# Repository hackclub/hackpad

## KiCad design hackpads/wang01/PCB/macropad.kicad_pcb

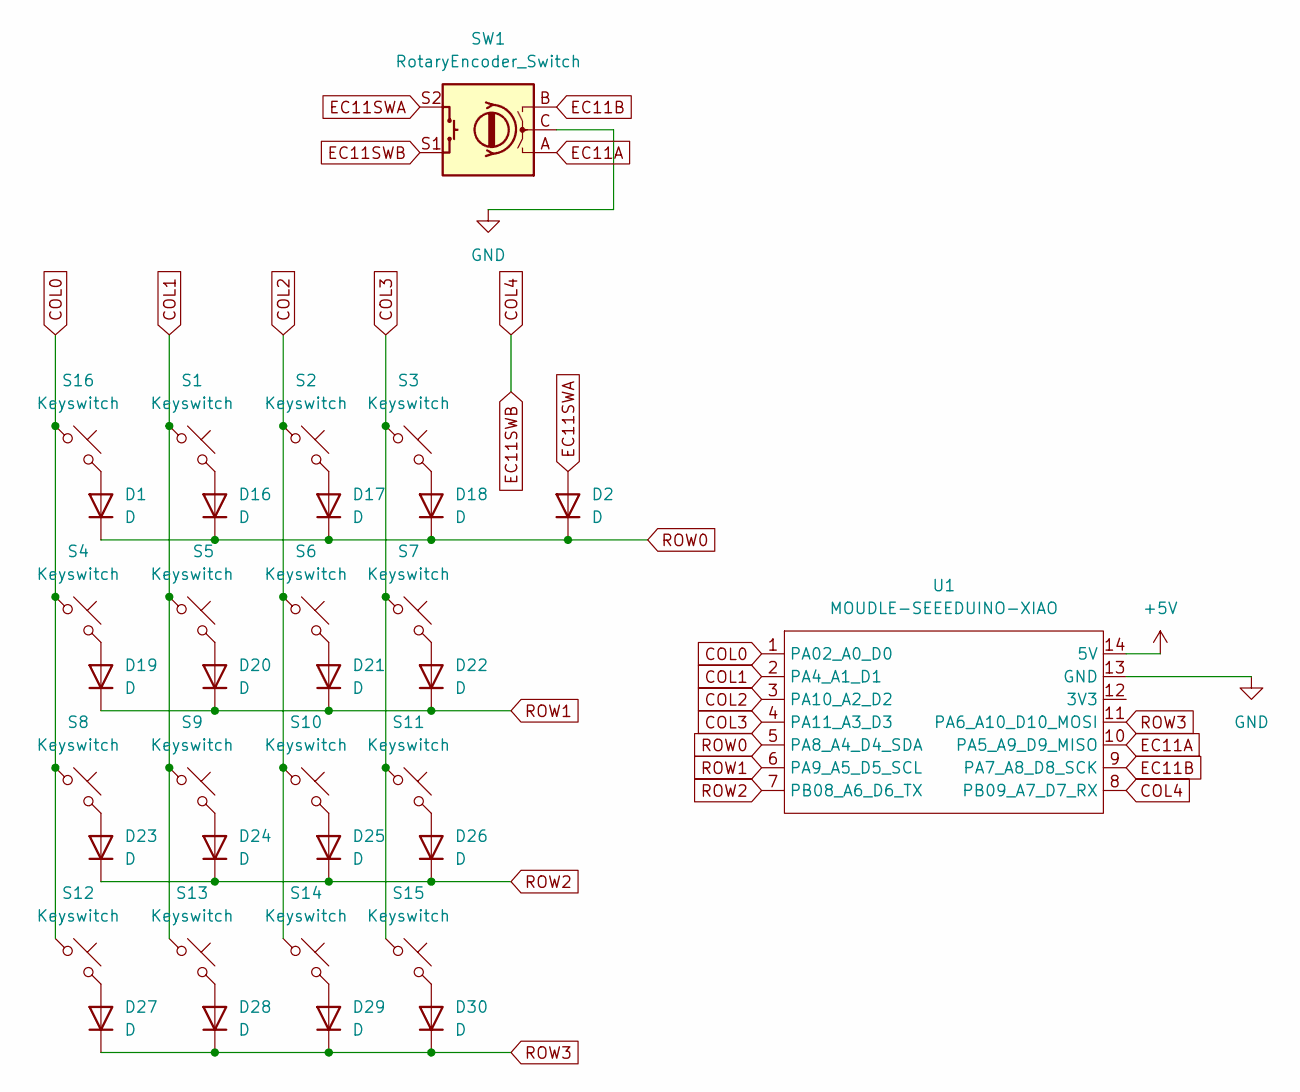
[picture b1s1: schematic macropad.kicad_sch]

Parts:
D1, D2, D16, D17, D18, D19, D20, D21, D22, D23, D24, D25, D26, D27, D28, D29, D30: D; Diode_DO-35
S1, S2, S3, S4, S5, S6, S7, S8, S9, S10, S11, S12, S13, S14, S15, S16: Keyswitch; MX-Solderable-1U
SW1: RotaryEncoder_Switch; RotaryEncoder_Alps_EC11E-Switch_Vertical_H20mm
U1: MOUDLE-SEEEDUINO-XIAO; MOUDLE14P-2.54-21X17.8MM

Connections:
+5V: U1.14 (5V)
COL0: S4.1, S8.1, S12.1, S16.1, U1.1 (PA02_A0_D0)
COL1: S1.1, S5.1, S9.1, S13.1, U1.2 (PA4_A1_D1)
COL2: S2.1, S6.1, S10.1, S14.1, U1.3 (PA10_A2_D2)
COL3: S3.1, S7.1, S11.1, S15.1, U1.4 (PA11_A3_D3)
COL4: SW1.S1, U1.8 (PB09_A7_D7_RX)
EC11A: SW1.A, U1.10 (PA5_A9_D9_MISO)
EC11B: SW1.B, U1.9 (PA7_A8_D8_SCK)
EC11SWA: D2.2 (A), SW1.S2
GND: SW1.C, U1.13 (GND)
unnamed: D1.2 (A), S16.2
unnamed: D16.2 (A), S1.2
unnamed: D17.2 (A), S2.2
unnamed: D18.2 (A), S3.2
unnamed: D19.2 (A), S4.2
unnamed: D20.2 (A), S5.2
unnamed: D21.2 (A), S6.2
unnamed: D22.2 (A), S7.2
unnamed: D23.2 (A), S8.2
unnamed: D24.2 (A), S9.2
unnamed: D25.2 (A), S10.2
unnamed: D26.2 (A), S11.2
unnamed: D27.2 (A), S12.2
unnamed: D28.2 (A), S13.2
unnamed: D29.2 (A), S14.2
unnamed: D30.2 (A), S15.2
ROW0: D1.1 (K), D2.1 (K), D16.1 (K), D17.1 (K), D18.1 (K), U1.5 (PA8_A4_D4_SDA)
ROW1: D19.1 (K), D20.1 (K), D21.1 (K), D22.1 (K), U1.6 (PA9_A5_D5_SCL)
ROW2: D23.1 (K), D24.1 (K), D25.1 (K), D26.1 (K), U1.7 (PB08_A6_D6_TX)
ROW3: D27.1 (K), D28.1 (K), D29.1 (K), D30.1 (K), U1.11 (PA6_A10_D10_MOSI)

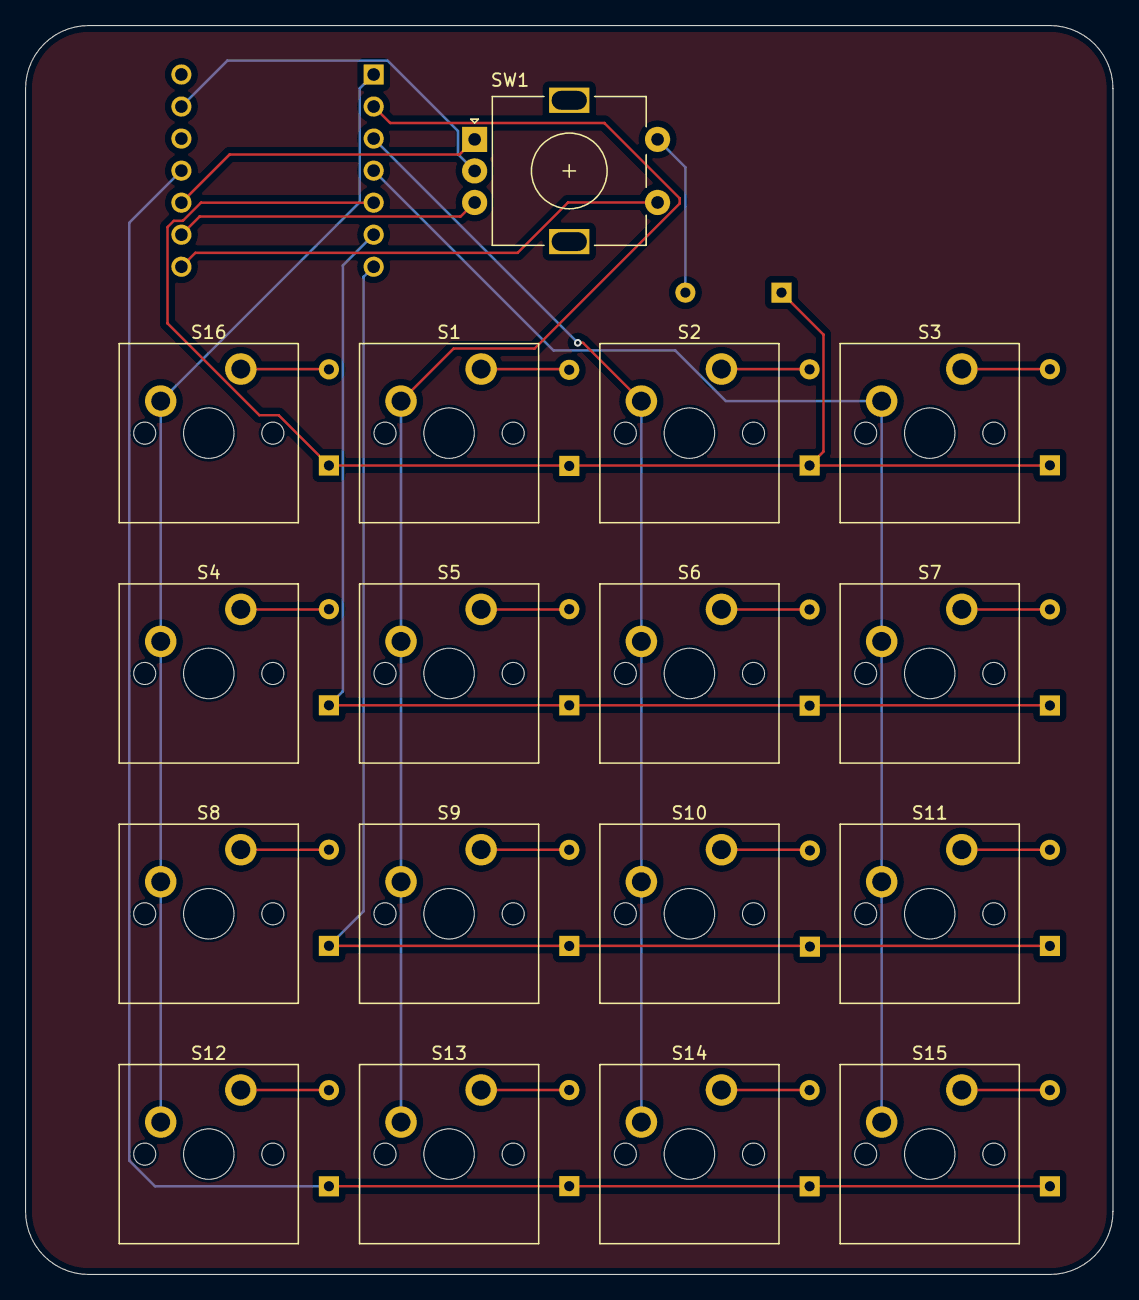
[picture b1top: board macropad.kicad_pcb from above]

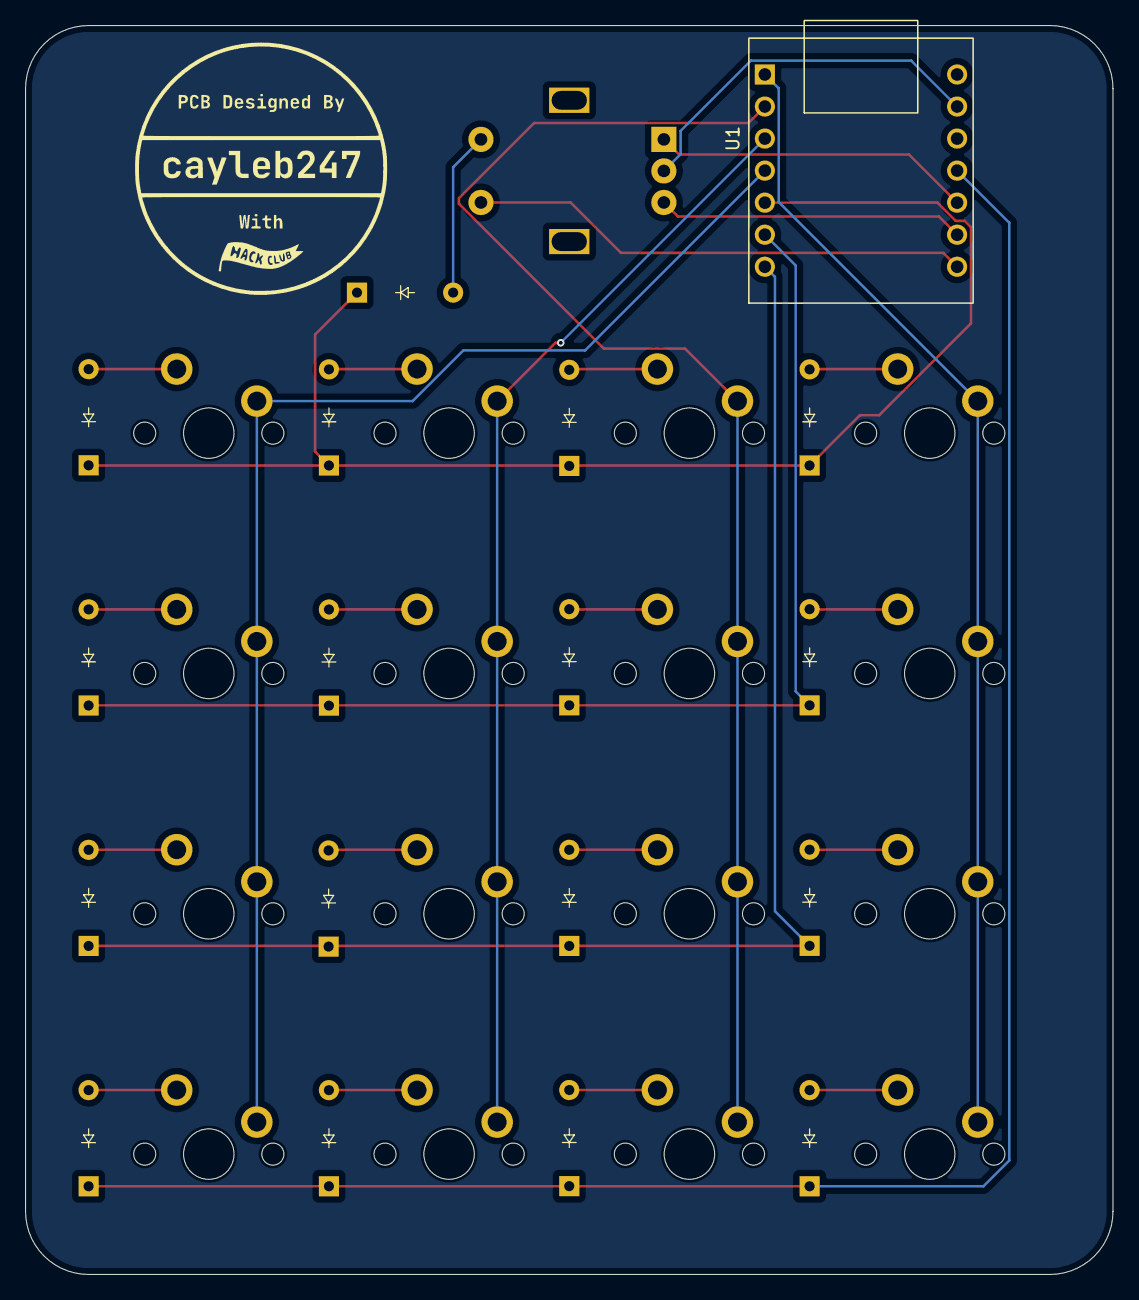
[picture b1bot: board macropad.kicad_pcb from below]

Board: 2 copper layers, 86.2 x 99.0 mm, 35 parts (18 on the bottom side), 29 nets.

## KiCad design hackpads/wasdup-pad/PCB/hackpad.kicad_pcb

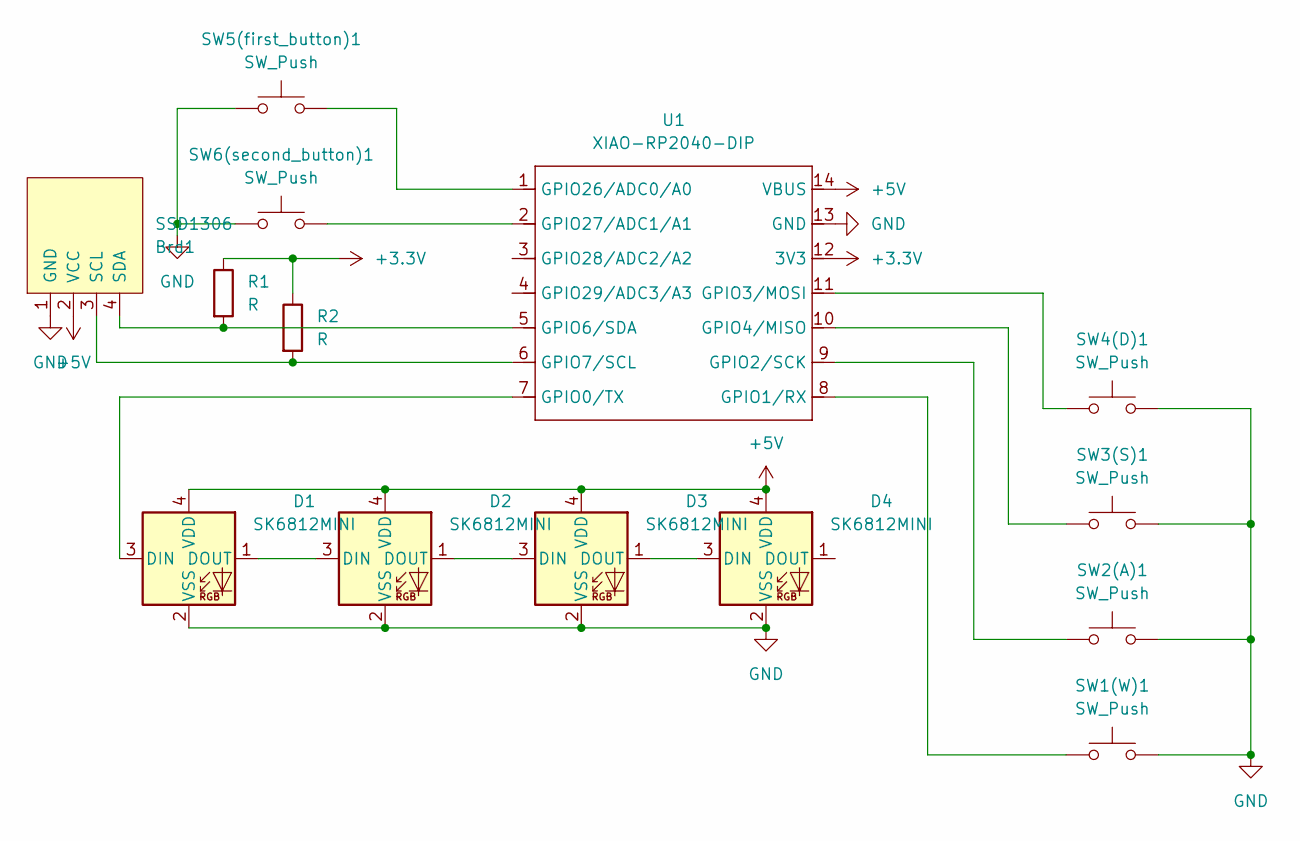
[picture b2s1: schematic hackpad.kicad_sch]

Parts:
Brd1: SSD1306; 128x64OLED
D1, D2, D3, D4: SK6812MINI; LED_SK6812MINI_PLCC4_3.5x3.5mm_P1.75mm
R1, R2: R; R_Axial_DIN0204_L3.6mm_D1.6mm_P7.62mm_Horizontal
SW1(W)1, SW2(A)1, SW3(S)1, SW4(D)1: SW_Push; SW_Cherry_MX_1.00u_PCB
SW5(first_button)1, SW6(second_button)1: SW_Push; SW_PUSH_6mm_H4.3mm
U1: XIAO-RP2040-DIP

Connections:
+3.3V: R1.1, R2.1, U1.12 (3V3)
+5V: Brd1.2 (VCC), D1.4 (VDD), D2.4 (VDD), D3.4 (VDD), D4.4 (VDD), U1.14 (VBUS)
GND: Brd1.1 (GND), D1.2 (VSS), D2.2 (VSS), D3.2 (VSS), D4.2 (VSS), SW1(W)1.2, SW2(A)1.2, SW3(S)1.2, SW4(D)1.2, SW5(first_button)1.1, SW6(second_button)1.1, U1.13 (GND)
unnamed: Brd1.3 (SCL), R2.2, U1.6 (GPIO7/SCL)
unnamed: Brd1.4 (SDA), R1.2, U1.5 (GPIO6/SDA)
unnamed: D1.3 (DIN), U1.7 (GPIO0/TX)
unnamed: D1.1 (DOUT), D2.3 (DIN)
unnamed: D2.1 (DOUT), D3.3 (DIN)
unnamed: D3.1 (DOUT), D4.3 (DIN)
unnamed: SW1(W)1.1, U1.8 (GPIO1/RX)
unnamed: SW2(A)1.1, U1.9 (GPIO2/SCK)
unnamed: SW4(D)1.1, U1.11 (GPIO3/MOSI)
unnamed: SW3(S)1.1, U1.10 (GPIO4/MISO)
unnamed: SW5(first_button)1.2, U1.1 (GPIO26/ADC0/A0)
unnamed: SW6(second_button)1.2, U1.2 (GPIO27/ADC1/A1)

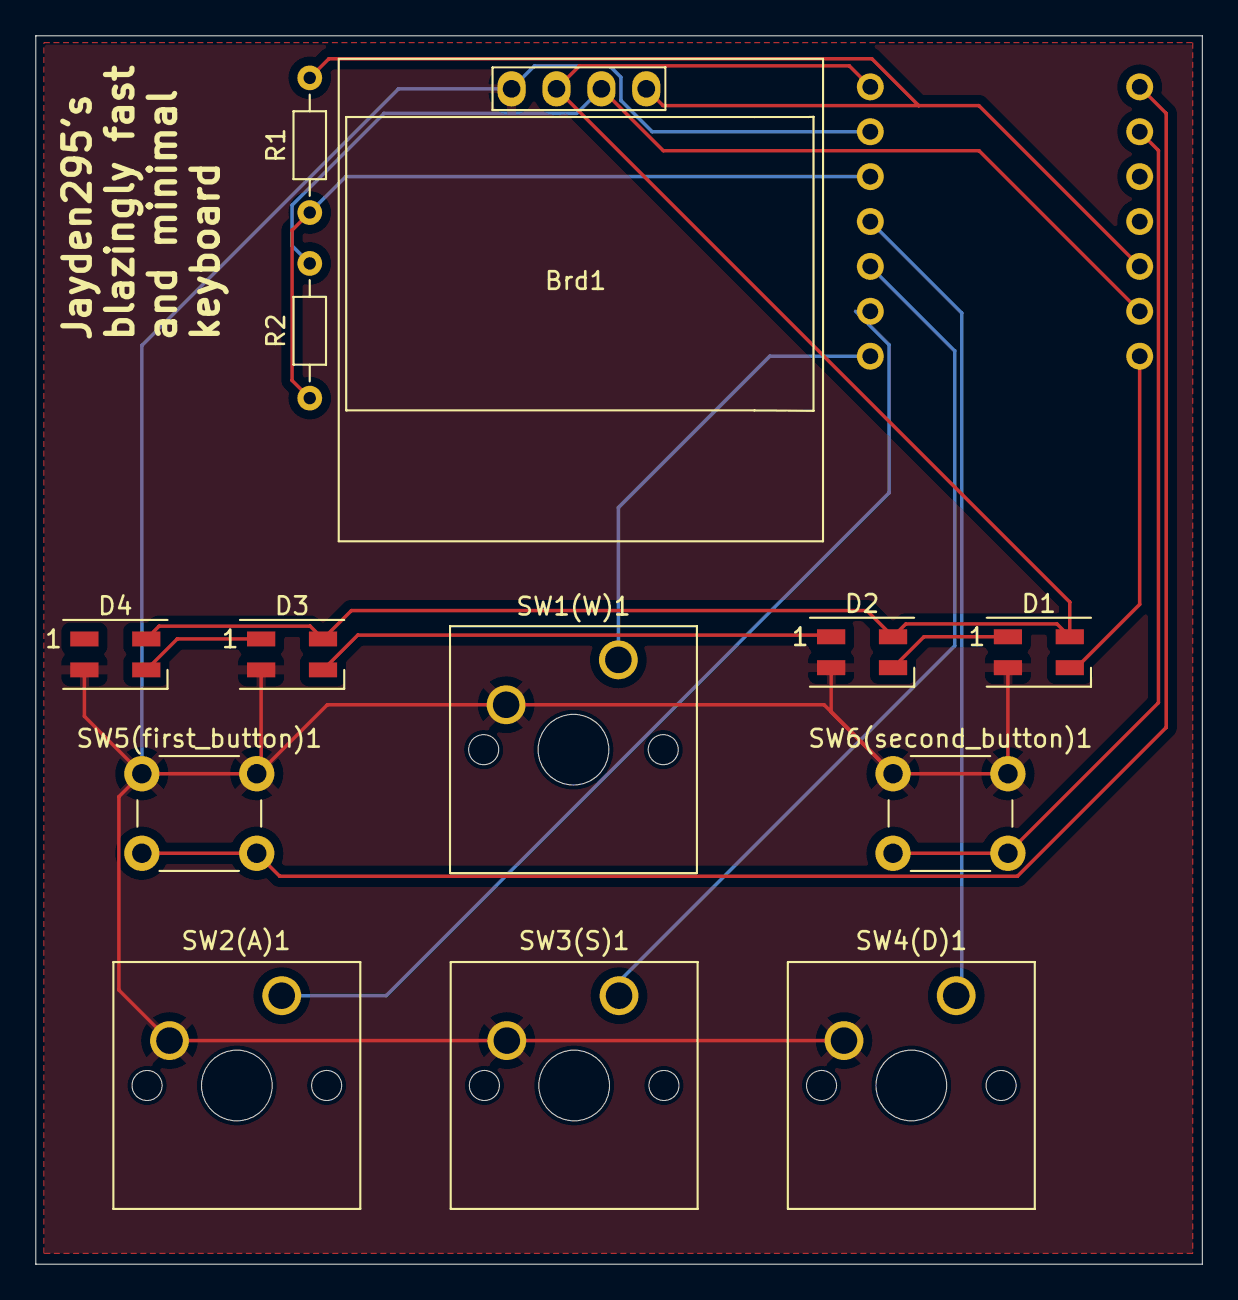
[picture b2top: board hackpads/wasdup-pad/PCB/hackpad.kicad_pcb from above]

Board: 2 copper layers, 66.0 x 69.5 mm, 14 parts (1 on the bottom side), 15 nets.

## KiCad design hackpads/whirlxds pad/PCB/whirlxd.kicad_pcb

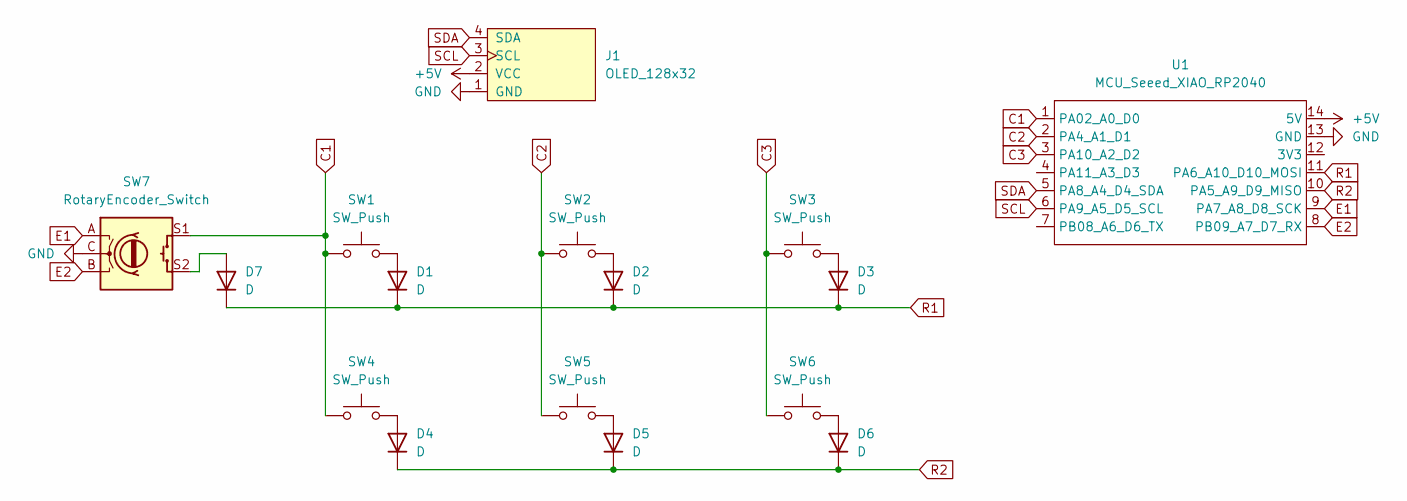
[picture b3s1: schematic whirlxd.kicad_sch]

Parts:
D1, D2, D3, D4, D5, D6, D7: D; D_SOD-523
J1: OLED_128x32; SSD1306-0.91-OLED-4pin-128x32 (2)
SW1, SW2, SW3, SW4, SW5, SW6: SW_Push; SW_Cherry_MX_1.00u_PCB
SW7: RotaryEncoder_Switch; RotaryEncoder_Alps_EC11E-Switch_Vertical_H20mm
U1: MCU_Seeed_XIAO_RP2040; XIAO-RP2040-DIP

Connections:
+5V: J1.2 (VCC), U1.14 (5V)
C1: SW1.1, SW4.1, SW7.S1, U1.1 (PA02_A0_D0)
C2: SW2.1, SW5.1, U1.2 (PA4_A1_D1)
C3: SW3.1, SW6.1, U1.3 (PA10_A2_D2)
E1: SW7.A, U1.9 (PA7_A8_D8_SCK)
E2: SW7.B, U1.8 (PB09_A7_D7_RX)
GND: J1.1 (GND), SW7.C, U1.13 (GND)
unnamed: D1.2 (A), SW1.2
unnamed: D2.2 (A), SW2.2
unnamed: D3.2 (A), SW3.2
unnamed: D4.2 (A), SW4.2
unnamed: D5.2 (A), SW5.2
unnamed: D6.2 (A), SW6.2
unnamed: D7.2 (A), SW7.S2
R1: D1.1 (K), D2.1 (K), D3.1 (K), D7.1 (K), U1.11 (PA6_A10_D10_MOSI)
R2: D4.1 (K), D5.1 (K), D6.1 (K), U1.10 (PA5_A9_D9_MISO)
SCL: J1.3 (SCL), U1.6 (PA9_A5_D5_SCL)
SDA: J1.4 (SDA), U1.5 (PA8_A4_D4_SDA)

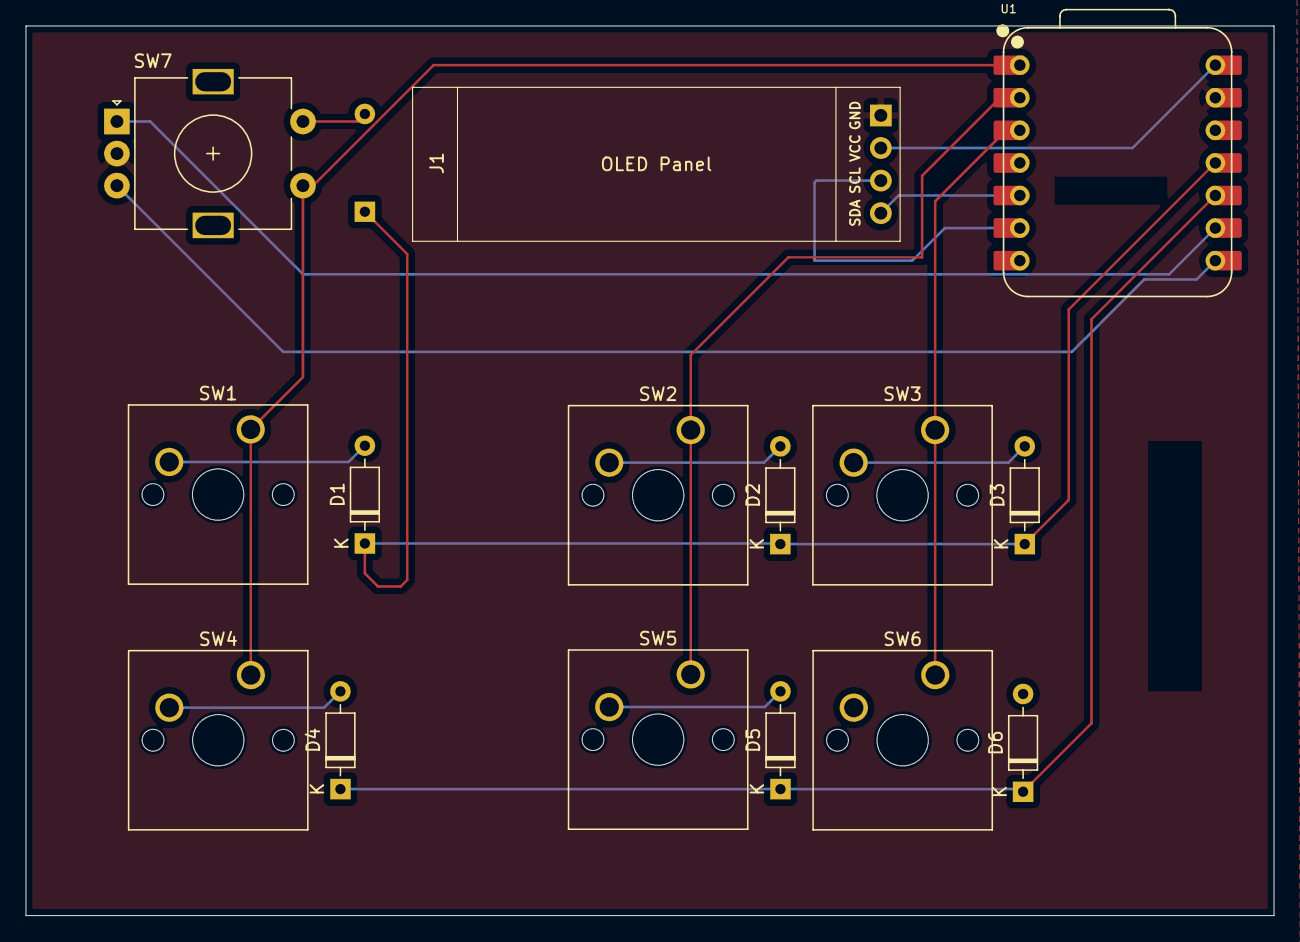
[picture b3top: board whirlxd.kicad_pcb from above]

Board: 2 copper layers, 97.3 x 69.3 mm, 16 parts (1 on the bottom side), 18 nets.

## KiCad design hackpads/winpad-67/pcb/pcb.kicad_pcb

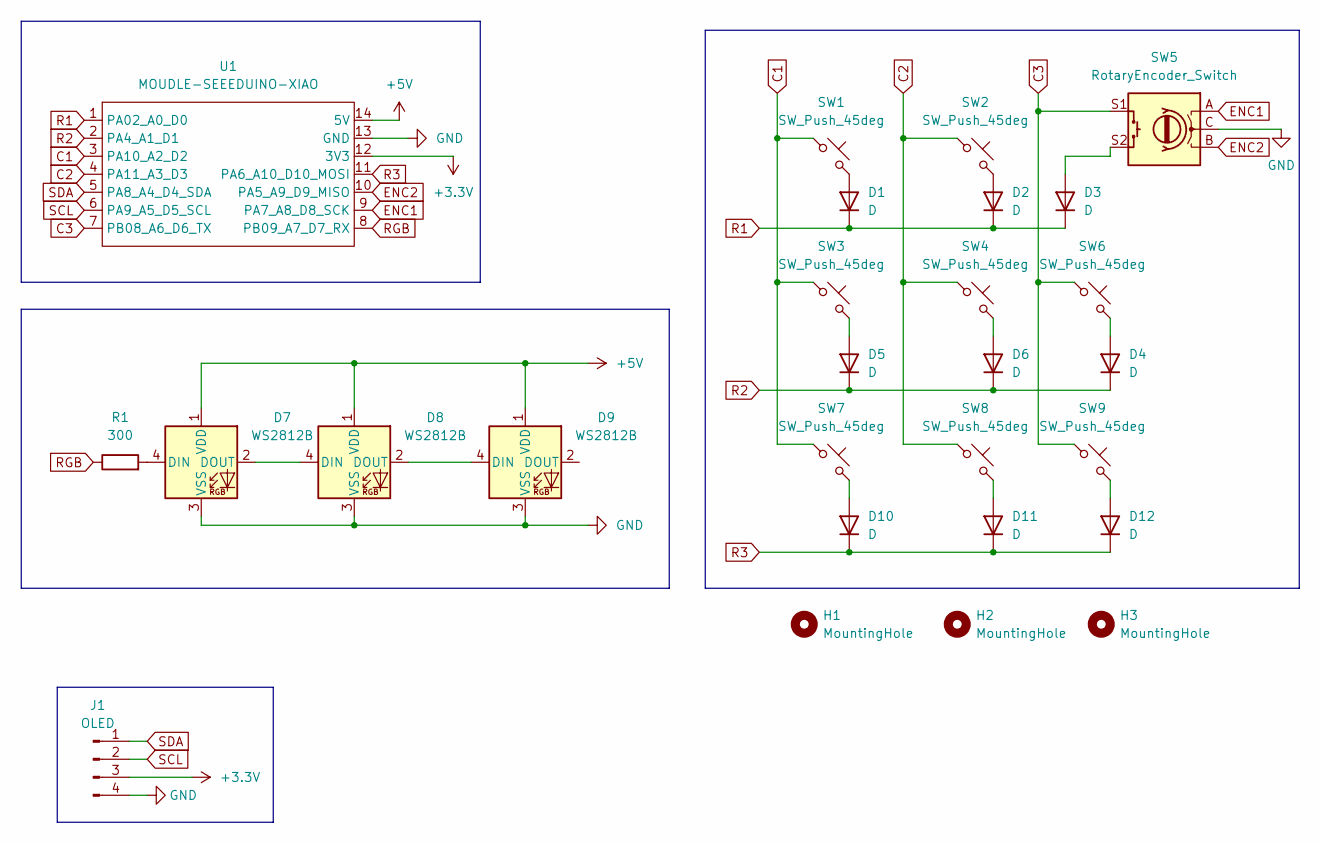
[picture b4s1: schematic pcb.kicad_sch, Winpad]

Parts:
D1, D2, D3, D4, D5, D6, D10, D11, D12: D; D_DO-35_SOD27_P7.62mm_Horizontal
D7, D8, D9: WS2812B; LED_WS2812B_PLCC4_5.0x5.0mm_P3.2mm
H1, H2, H3: MountingHole; MountingHole_2.2mm_M2
J1: OLED; PinHeader_1x04_P2.54mm_Vertical
R1: 300; R_Axial_DIN0207_L6.3mm_D2.5mm_P10.16mm_Horizontal
SW1, SW2, SW3, SW4, SW6, SW7, SW8, SW9: SW_Push_45deg; SW_Cherry_MX_1.00u_PCB
SW5: RotaryEncoder_Switch; RotaryEncoder_Alps_EC11E-Switch_Vertical_H20mm
U1: MOUDLE-SEEEDUINO-XIAO; MOUDLE14P-2.54-21X17.8MM

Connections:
+3.3V: J1.3, U1.12 (3V3)
+5V: D7.1 (VDD), D8.1 (VDD), D9.1 (VDD), U1.14 (5V)
C1: SW1.1, SW3.1, SW7.1, U1.3 (PA10_A2_D2)
C2: SW2.1, SW4.1, SW8.1, U1.4 (PA11_A3_D3)
C3: SW5.S1, SW6.1, SW9.1, U1.7 (PB08_A6_D6_TX)
ENC1: SW5.A, U1.9 (PA7_A8_D8_SCK)
ENC2: SW5.B, U1.10 (PA5_A9_D9_MISO)
GND: D7.3 (VSS), D8.3 (VSS), D9.3 (VSS), J1.4, SW5.C, U1.13 (GND)
unnamed: D1.2 (A), SW1.2
unnamed: D2.2 (A), SW2.2
unnamed: D3.2 (A), SW5.S2
unnamed: D4.2 (A), SW6.2
unnamed: D5.2 (A), SW3.2
unnamed: D6.2 (A), SW4.2
unnamed: D7.4 (DIN), R1.2
unnamed: D7.2 (DOUT), D8.4 (DIN)
unnamed: D8.2 (DOUT), D9.4 (DIN)
unnamed: D10.2 (A), SW7.2
unnamed: D11.2 (A), SW8.2
unnamed: D12.2 (A), SW9.2
R1: D1.1 (K), D2.1 (K), D3.1 (K), U1.1 (PA02_A0_D0)
R2: D4.1 (K), D5.1 (K), D6.1 (K), U1.2 (PA4_A1_D1)
R3: D10.1 (K), D11.1 (K), D12.1 (K), U1.11 (PA6_A10_D10_MOSI)
RGB: R1.1, U1.8 (PB09_A7_D7_RX)
SCL: J1.2, U1.6 (PA9_A5_D5_SCL)
SDA: J1.1, U1.5 (PA8_A4_D4_SDA)

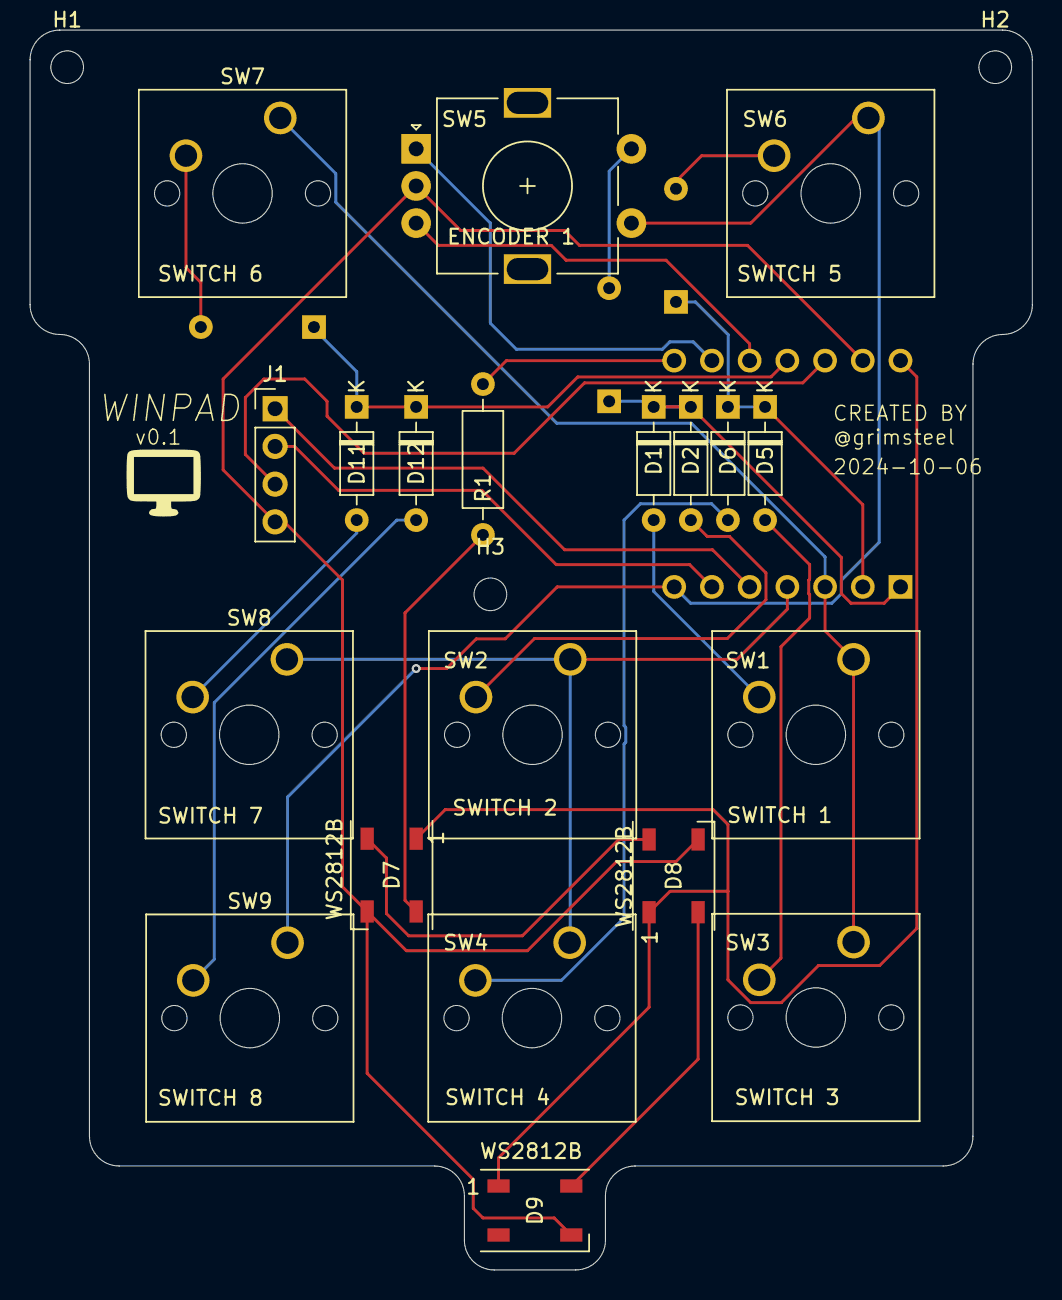
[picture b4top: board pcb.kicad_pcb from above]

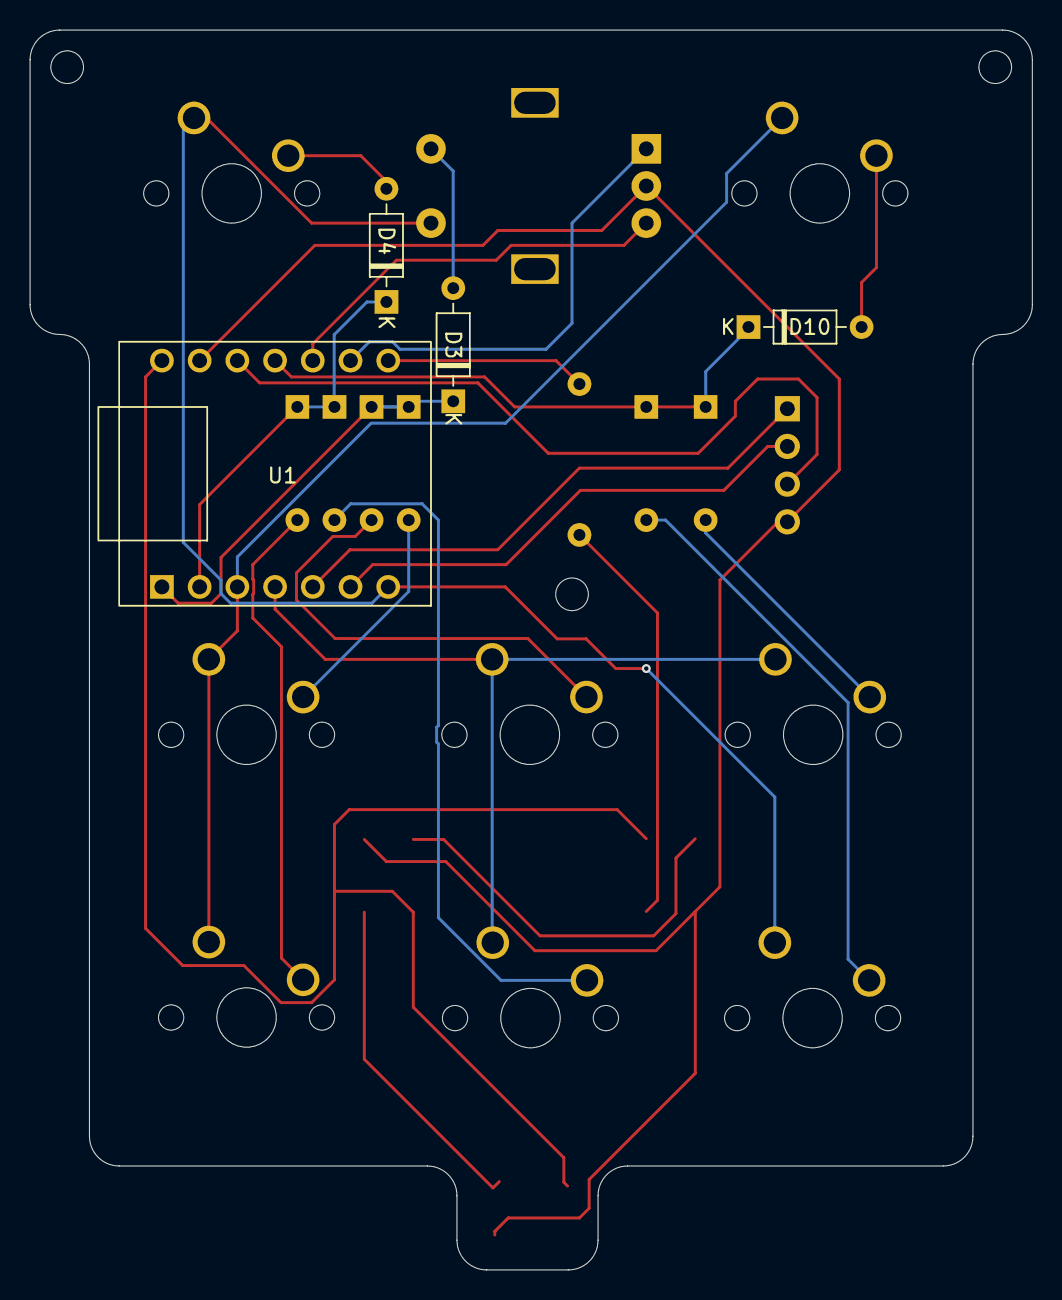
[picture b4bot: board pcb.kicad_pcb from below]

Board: 2 copper layers, 67.5 x 83.5 mm, 27 parts (4 on the bottom side), 26 nets.

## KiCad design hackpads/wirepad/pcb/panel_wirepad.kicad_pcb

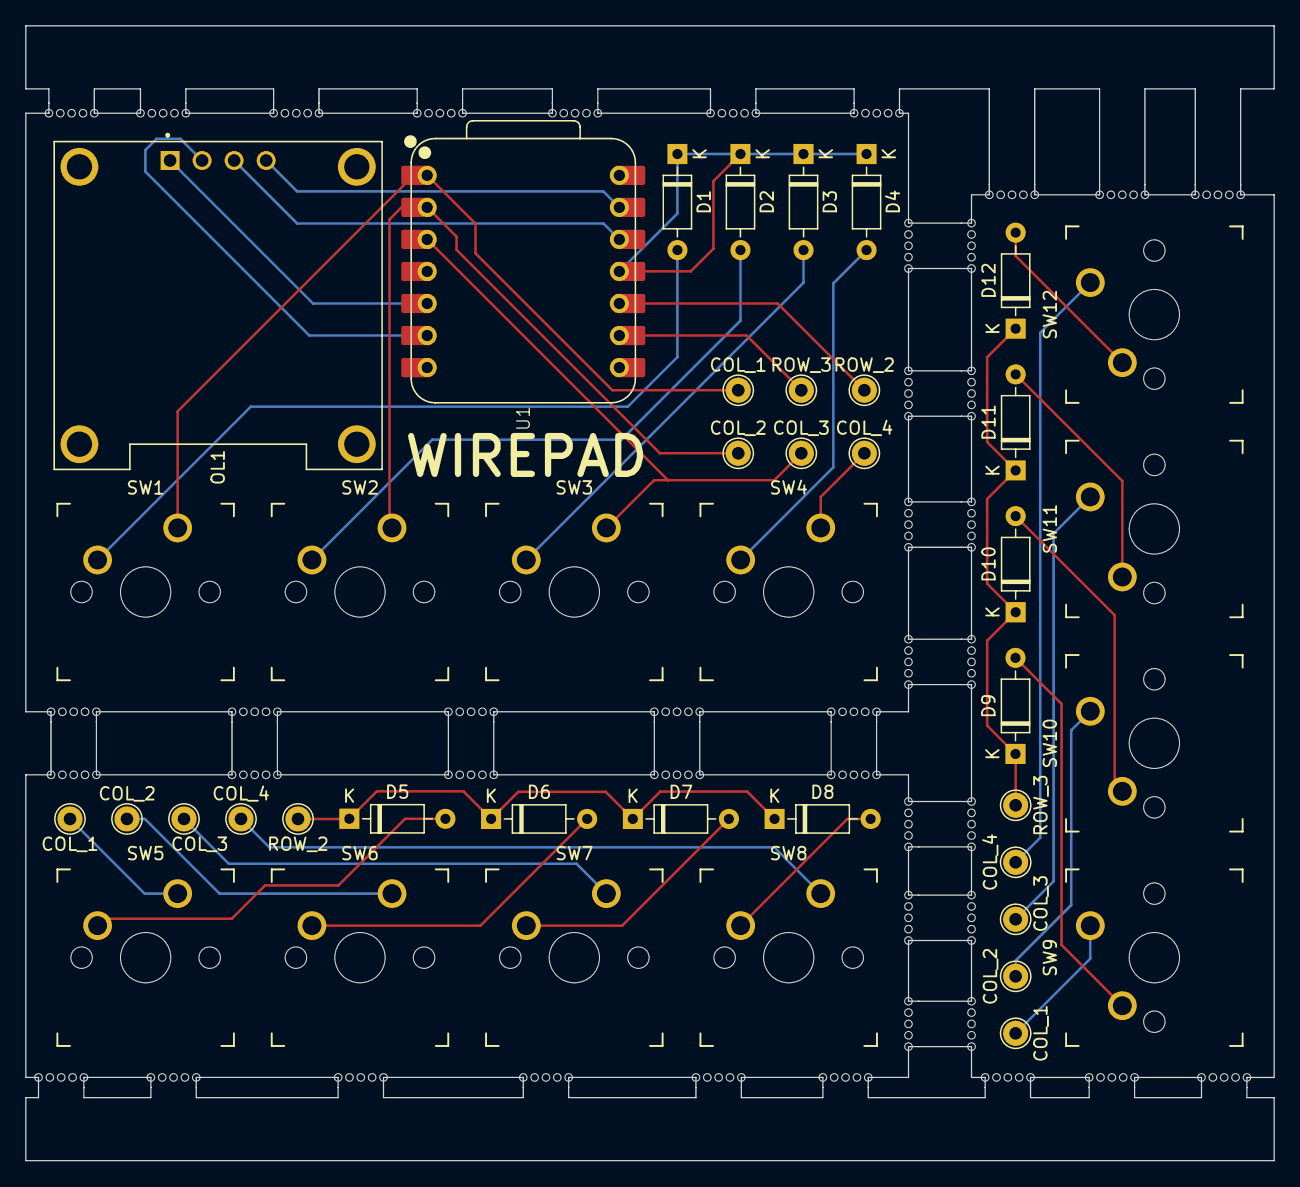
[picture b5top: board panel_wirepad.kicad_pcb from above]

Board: 2 copper layers, 99.0 x 90.0 mm, 257 parts (0 on the bottom side), 23 nets.

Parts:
COL_1, COL_1#2, COL_1#3, COL_2, COL_2#2, COL_2#3, COL_3, COL_3#2, COL_3#3, COL_4, COL_4#2, COL_4#3: TestPoint_THTPad_D2.0mm_Drill1.0mm
D1, D2, D3, D4, D5, D6, D7, D8, D9, D10, D11, D12: 1N4148; D_DO-35_SOD27_P7.62mm_Horizontal
KiKit_MB_1_1, KiKit_MB_1_2, KiKit_MB_1_3, KiKit_MB_1_4, KiKit_MB_1_5, KiKit_MB_2_1, KiKit_MB_2_2, KiKit_MB_2_3, KiKit_MB_2_4, KiKit_MB_2_5, KiKit_MB_3_1, KiKit_MB_3_2, KiKit_MB_3_3, KiKit_MB_3_4, KiKit_MB_3_5, KiKit_MB_4_1, KiKit_MB_4_2, KiKit_MB_4_3, KiKit_MB_4_4, KiKit_MB_4_5, KiKit_MB_5_1, KiKit_MB_5_2, KiKit_MB_5_3, KiKit_MB_5_4, KiKit_MB_5_5, KiKit_MB_6_1, KiKit_MB_6_2, KiKit_MB_6_3, KiKit_MB_6_4, KiKit_MB_6_5, KiKit_MB_7_1, KiKit_MB_7_2, KiKit_MB_7_3, KiKit_MB_7_4, KiKit_MB_7_5, KiKit_MB_8_1, KiKit_MB_8_2, KiKit_MB_8_3, KiKit_MB_8_4, KiKit_MB_8_5, KiKit_MB_9_1, KiKit_MB_9_2, KiKit_MB_9_3, KiKit_MB_9_4, KiKit_MB_9_5, KiKit_MB_10_1, KiKit_MB_10_2, KiKit_MB_10_3, KiKit_MB_10_4, KiKit_MB_10_5, KiKit_MB_11_1, KiKit_MB_11_2, KiKit_MB_11_3, KiKit_MB_11_4, KiKit_MB_11_5, KiKit_MB_12_1, KiKit_MB_12_2, KiKit_MB_12_3, KiKit_MB_12_4, KiKit_MB_12_5, KiKit_MB_13_1, KiKit_MB_13_2, KiKit_MB_13_3, KiKit_MB_13_4, KiKit_MB_13_5, KiKit_MB_14_1, KiKit_MB_14_2, KiKit_MB_14_3, KiKit_MB_14_4, KiKit_MB_14_5, KiKit_MB_15_1, KiKit_MB_15_2, KiKit_MB_15_3, KiKit_MB_15_4, KiKit_MB_15_5, KiKit_MB_16_1, KiKit_MB_16_2, KiKit_MB_16_3, KiKit_MB_16_4, KiKit_MB_16_5, KiKit_MB_17_1, KiKit_MB_17_2, KiKit_MB_17_3, KiKit_MB_17_4, KiKit_MB_17_5, KiKit_MB_18_1, KiKit_MB_18_2, KiKit_MB_18_3, KiKit_MB_18_4, KiKit_MB_18_5, KiKit_MB_19_1, KiKit_MB_19_2, KiKit_MB_19_3, KiKit_MB_19_4, KiKit_MB_19_5, KiKit_MB_20_1, KiKit_MB_20_2, KiKit_MB_20_3, KiKit_MB_20_4, KiKit_MB_20_5, KiKit_MB_21_1, KiKit_MB_21_2, KiKit_MB_21_3, KiKit_MB_21_4, KiKit_MB_21_5, KiKit_MB_22_1, KiKit_MB_22_2, KiKit_MB_22_3, KiKit_MB_22_4, KiKit_MB_22_5, KiKit_MB_23_1, KiKit_MB_23_2, KiKit_MB_23_3, KiKit_MB_23_4, KiKit_MB_23_5, KiKit_MB_24_1, KiKit_MB_24_2, KiKit_MB_24_3, KiKit_MB_24_4, KiKit_MB_24_5, KiKit_MB_25_1, KiKit_MB_25_2, KiKit_MB_25_3, KiKit_MB_25_4, KiKit_MB_25_5, KiKit_MB_26_1, KiKit_MB_26_2, KiKit_MB_26_3, KiKit_MB_26_4, KiKit_MB_26_5, KiKit_MB_27_1, KiKit_MB_27_2, KiKit_MB_27_3, KiKit_MB_27_4, KiKit_MB_27_5, KiKit_MB_28_1, KiKit_MB_28_2, KiKit_MB_28_3, KiKit_MB_28_4, KiKit_MB_28_5, KiKit_MB_29_1, KiKit_MB_29_2, KiKit_MB_29_3, KiKit_MB_29_4, KiKit_MB_29_5, KiKit_MB_30_1, KiKit_MB_30_2, KiKit_MB_30_3, KiKit_MB_30_4, KiKit_MB_30_5, KiKit_MB_31_1, KiKit_MB_31_2, KiKit_MB_31_3, KiKit_MB_31_4, KiKit_MB_31_5, KiKit_MB_32_1, KiKit_MB_32_2, KiKit_MB_32_3, KiKit_MB_32_4, KiKit_MB_32_5, KiKit_MB_33_1, KiKit_MB_33_2, KiKit_MB_33_3, KiKit_MB_33_4, KiKit_MB_33_5, KiKit_MB_34_1, KiKit_MB_34_2, KiKit_MB_34_3, KiKit_MB_34_4, KiKit_MB_34_5, KiKit_MB_35_1, KiKit_MB_35_2, KiKit_MB_35_3, KiKit_MB_35_4, KiKit_MB_35_5, KiKit_MB_36_1, KiKit_MB_36_2, KiKit_MB_36_3, KiKit_MB_36_4, KiKit_MB_36_5, KiKit_MB_37_1, KiKit_MB_37_2, KiKit_MB_37_3, KiKit_MB_37_4, KiKit_MB_37_5, KiKit_MB_38_1, KiKit_MB_38_2, KiKit_MB_38_3, KiKit_MB_38_4, KiKit_MB_38_5, KiKit_MB_39_1, KiKit_MB_39_2, KiKit_MB_39_3, KiKit_MB_39_4, KiKit_MB_39_5, KiKit_MB_40_1, KiKit_MB_40_2, KiKit_MB_40_3, KiKit_MB_40_4, KiKit_MB_40_5, KiKit_MB_41_1, KiKit_MB_41_2, KiKit_MB_41_3, KiKit_MB_41_4, KiKit_MB_41_5, KiKit_MB_42_1, KiKit_MB_42_2, KiKit_MB_42_3, KiKit_MB_42_4, KiKit_MB_42_5, KiKit_MB_43_1, KiKit_MB_43_2, KiKit_MB_43_3, KiKit_MB_43_4, KiKit_MB_43_5: NPTH
OL1: OLED; module_dm-oled096-636
ROW_2, ROW_2#2, ROW_3, ROW_3#2: TestPoint_THTPad_D2.0mm_Drill1.0mm
SW1, SW2, SW3, SW4, SW5, SW6, SW7, SW8, SW9, SW10, SW11, SW12: SW_Push_45deg; SW_MX
U1: XIAO-RP2040-DIP

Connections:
+3V3: OL1.3 (VCC), U1.12 (3V3)
COL_1: COL_1.2, COL_1#2.2, COL_1#3.2, SW1.1, SW5.1, SW9.1, U1.1 (GPIO26/ADC0/A0)
COL_2: COL_2.1, COL_2#2.1, COL_2#3.1, SW2.1, SW6.1, SW10.1, U1.2 (GPIO27/ADC1/A1)
COL_3: COL_3.3, COL_3#2.3, COL_3#3.3, SW3.1, SW7.1, SW11.1, U1.3 (GPIO28/ADC2/A2)
COL_4: COL_4.6, COL_4#2.6, COL_4#3.6, SW4.1, SW8.1, SW12.1, U1.4 (GPIO29/ADC3/A3)
GND: OL1.4 (GND), U1.13 (GND)
unnamed: D1.2 (A), SW1.2
unnamed: D2.2 (A), SW2.2
unnamed: D3.2 (A), SW3.2
unnamed: D4.2 (A), SW4.2
unnamed: D5.2 (A), SW5.2
unnamed: D6.2 (A), SW6.2
unnamed: D7.2 (A), SW7.2
unnamed: D8.2 (A), SW8.2
unnamed: D9.2 (A), SW9.2
unnamed: D10.2 (A), SW10.2
unnamed: D11.2 (A), SW11.2
unnamed: D12.2 (A), SW12.2
ROW_1: D1.1 (K), D2.1 (K), D3.1 (K), D4.1 (K), U1.11 (GPIO3/MOSI)
ROW_2: D5.1 (K), D6.1 (K), D7.1 (K), D8.1 (K), ROW_2.5, ROW_2#2.5, U1.10 (GPIO4/MISO)
ROW_3: D9.1 (K), D10.1 (K), D11.1 (K), D12.1 (K), ROW_3.4, ROW_3#2.4, U1.9 (GPIO2/SCK)
SCL: OL1.2 (SCL), U1.6 (GPIO7/SCL)
SDA: OL1.1 (SDA), U1.5 (GPIO6/SDA)

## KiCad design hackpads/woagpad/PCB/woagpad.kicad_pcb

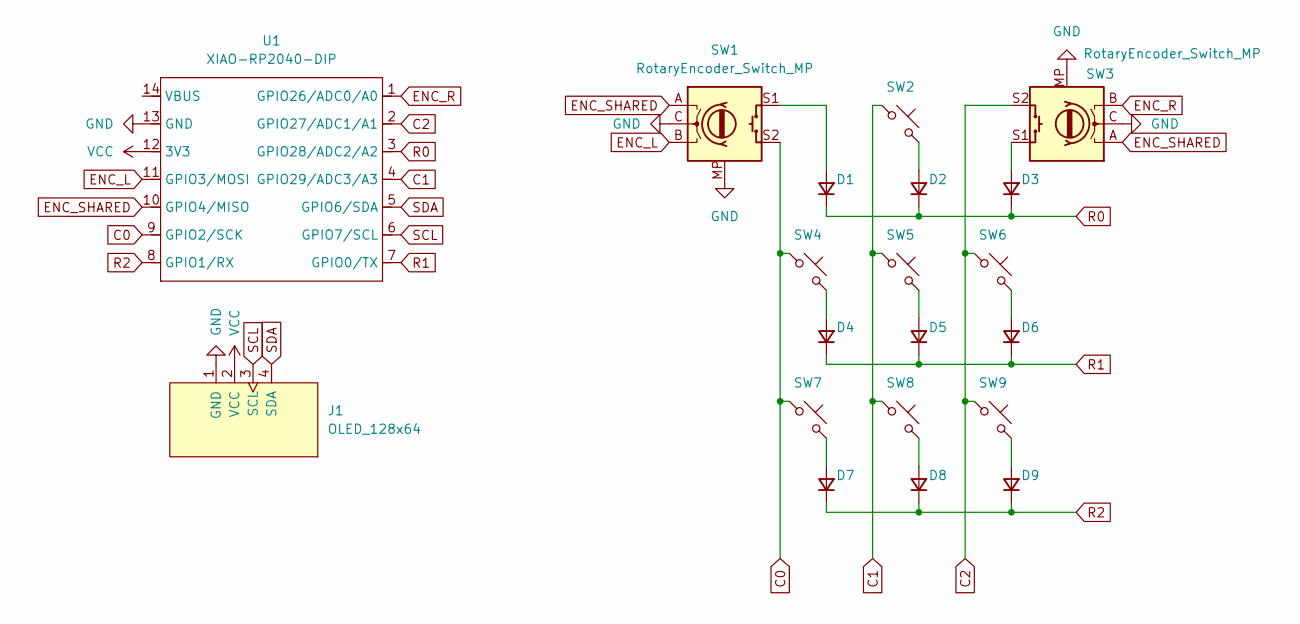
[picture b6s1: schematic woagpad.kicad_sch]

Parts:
D1, D2, D3, D4, D5, D6, D7, D8, D9: D; Diode_DO-35
J1: OLED_128x64; MODULE_DM-OLED096-636
SW1, SW3: RotaryEncoder_Switch_MP; Encoder_EC11_MX
SW2, SW4, SW5, SW6, SW7, SW8, SW9: SW_Push; MX_PCB
U1: XIAO-RP2040-DIP; Seeed_XIAO_RP2040

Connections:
C0: SW1.S2, SW4.1, SW7.1, U1.9 (GPIO2/SCK)
C1: SW2.1, SW5.1, SW8.1, U1.4 (GPIO29/ADC3/A3)
C2: SW3.S2, SW6.1, SW9.1, U1.2 (GPIO27/ADC1/A1)
ENC_L: SW1.B, U1.11 (GPIO3/MOSI)
ENC_R: SW3.B, U1.1 (GPIO26/ADC0/A0)
ENC_SHARED: SW1.A, SW3.A, U1.10 (GPIO4/MISO)
GND: J1.1 (GND), SW1.C, SW1.MP, SW3.C, SW3.MP, U1.13 (GND)
unnamed: D1.2 (A), SW1.S1
unnamed: D2.2 (A), SW2.2
unnamed: D3.2 (A), SW3.S1
unnamed: D4.2 (A), SW4.2
unnamed: D5.2 (A), SW5.2
unnamed: D6.2 (A), SW6.2
unnamed: D7.2 (A), SW7.2
unnamed: D8.2 (A), SW8.2
unnamed: D9.2 (A), SW9.2
R0: D1.1 (K), D2.1 (K), D3.1 (K), U1.3 (GPIO28/ADC2/A2)
R1: D4.1 (K), D5.1 (K), D6.1 (K), U1.7 (GPIO0/TX)
R2: D7.1 (K), D8.1 (K), D9.1 (K), U1.8 (GPIO1/RX)
SCL: J1.3 (SCL), U1.6 (GPIO7/SCL)
SDA: J1.4 (SDA), U1.5 (GPIO6/SDA)
VCC: J1.2 (VCC), U1.12 (3V3)
